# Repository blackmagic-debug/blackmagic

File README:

See https://github.com/blacksphere/blackmagic/wiki

Join the chat at https://gitter.im/blacksphere/blackmagic

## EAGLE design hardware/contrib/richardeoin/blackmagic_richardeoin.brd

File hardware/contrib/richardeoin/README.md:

This variant attempts to be as faithful to the Blackmagic mini as
possible, but also has several differences. This board has been built
and functions.

![Blackmagic richardeoin PCB](blackmagic_richardeoin_board.png
 "Blackmagic richardeoin PCB")
![Blackmagic richardeoin Assembled](blackmagic_richardeoin_assembled.JPG
 "Blackmagic richardeoin Assembled")

## Details

* The schematic and board have both been designed using Cadsoft EAGLE
  v6.4.0.

* The board size is 40mm x 16mm.

* The programming connector is an ARM 10-PIN Interface as described
  [here](http://www.keil.com/support/man/docs/ulink2/ulink2_hw_connectors.htm).

## Differences

### Uses 0603 [1608 Metric] components

The layout is intended for reflow soldering.

### Includes Level Translator

This board incorporates the same level translator used in the
full-sized Blackmagic, so it can be used to safely program 2.7V or
1.8V systems.

### USART Connector

The STM32F103's USART1 peripheral is broken out into a 0.1"
header. The hole centres are
[slightly offset to allow a press-fit](https://www.sparkfun.com/tutorials/114).

### BOOT0 Button

As well as the standard button for entering USB DFU mode, this variant
also provides a button for pulling the BOOT0 pin high to activate the
STM32 SystemMemory bootloader. Hold this button when plugging in the
module to enter then bootloader mode. Then
[scripts/bootprog.py](scripts/bootprog.py) can be used to program and
reprogram the chip over the USART1 interface.

This is useful for programming a brand new or 'bricked' blackmagic
with the DFU firmware (src/blackmagic_dfu.bin), the standard DFU mode
should be used for regular firmware updates.

## Parts and Costings

* [Parts List](Parts.md)

Parts Cost (Approximate): £14 + VAT
([uk.farnell.com](http://uk.farnell.com) August 2013)

Programming Cable: £8.49 + VAT
([uk.farnell.com](http://uk.farnell.com/samtec/ffsd-05-d-06-00-01-n/ribbon-cable-idc-152-4mm-grey-10way/dp/1667659)
August 2013)

## Assembly Photos

### Blank PCB:

### Solder Paste Stencil:

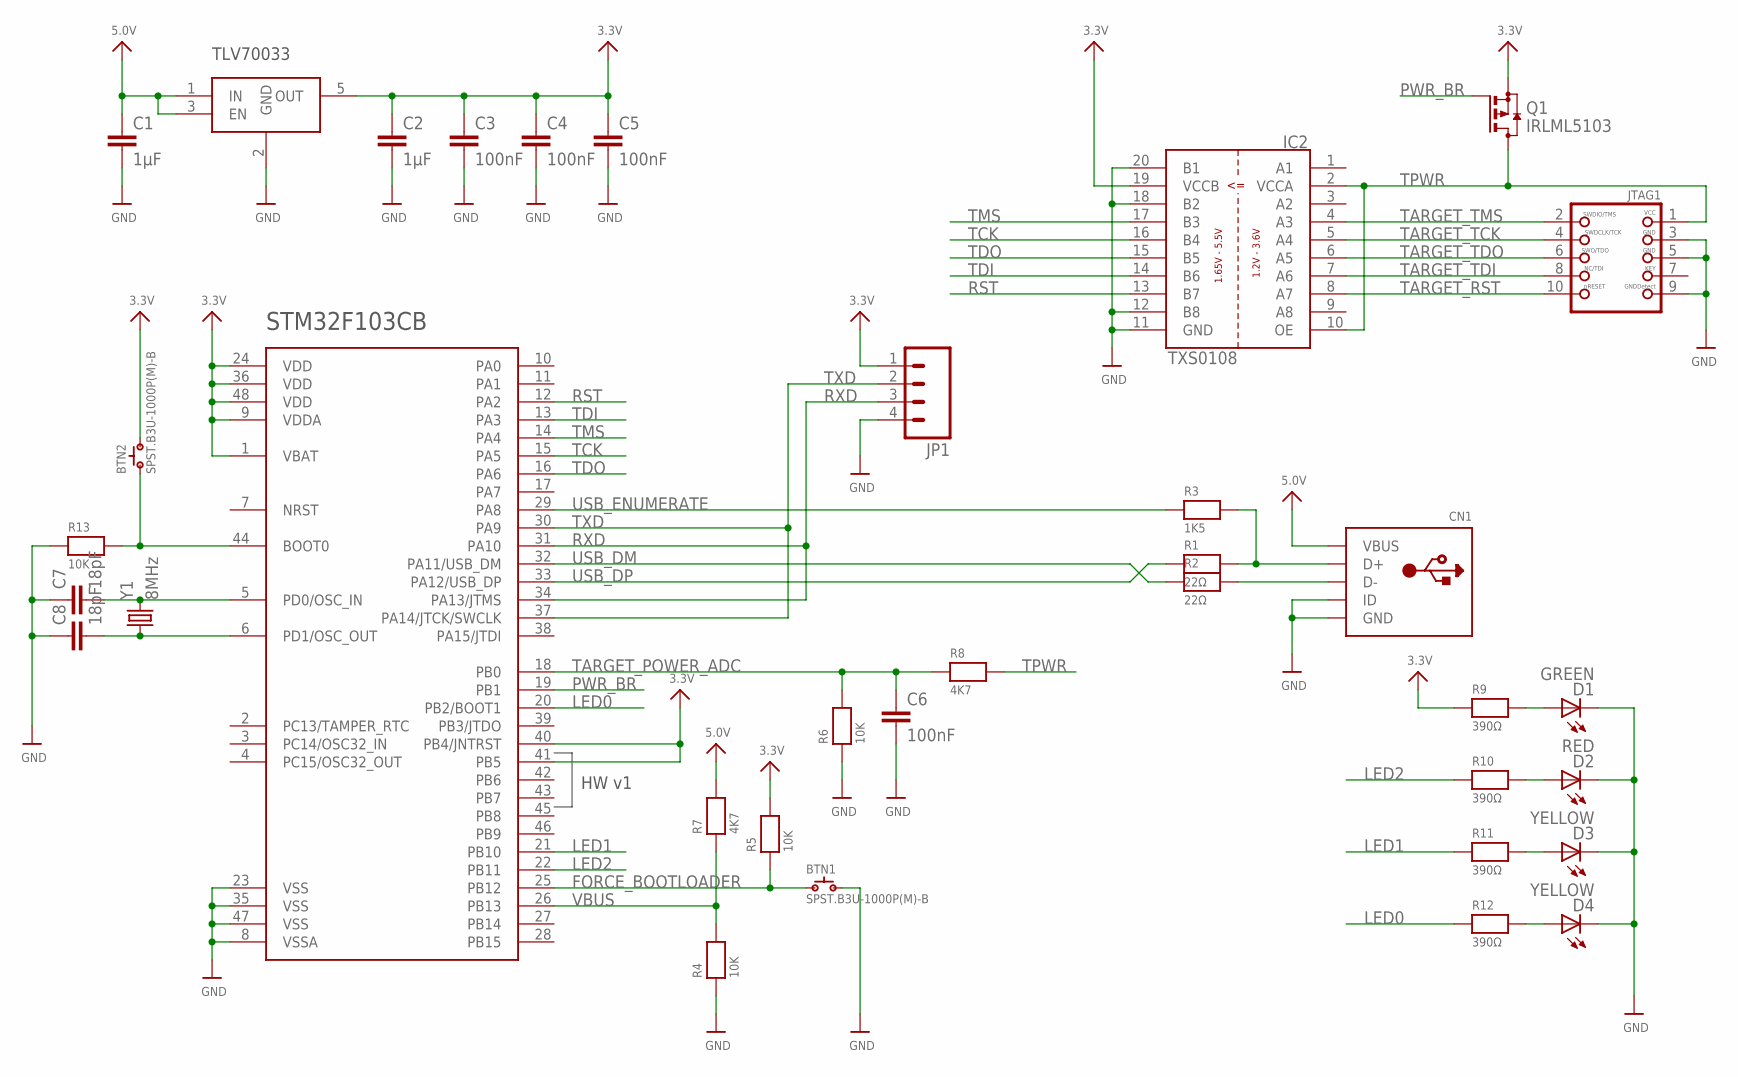
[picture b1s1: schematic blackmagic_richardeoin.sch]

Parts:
BTN1, BTN2: SPST.B3U-1000P(M)-B; B3U-1000P(M)-B
C1, C2: 1µF; C0603K
C3, C4, C5, C6: 100nF; C0603K
C7, C8: 18pF; C0603K
CN1: USBMINIB; USB-MINIB
D1: GREEN; CHIPLED_0603
D2: RED; CHIPLED_0603
D3, D4: YELLOW; CHIPLED_0603
IC1: STM32F_48PIN; TQFP48
IC2: TXS0108; TSSOP20
IC3: TLV70033DCK; SC70-5L
JP1: M04LOCK; 1X04_LOCK
JTAG1: JTAG-CORTEXM3; 2X05_1.27MM_SMT
Q1: IRLML5103; SOT23
R1, R2: 22Ω; 0603-MINI
R3: 1K5; 0603-MINI
R4, R5, R6, R13: 10K; 0603-MINI
R7, R8: 4K7; 0603-MINI
R9, R10, R11, R12: 390Ω; 0603-MINI
Y1: 8MHz; CRYSTAL-SMD-5X3

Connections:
3.3V: BTN2.2, C2.1, C3.1, C4.1, C5.1, IC1.1 (VBAT), IC1.9 (VDDA), IC1.24 (VDD), IC1.36 (VDD), IC1.40 (PB4/JNTRST), IC1.41 (PB5), IC1.48 (VDD), IC2.19 (VCCB), IC3.5 (OUT), JP1.1, Q1.2 (S), R5.2, R9.1
5.0V: C1.1, CN1.VBUS, IC3.1 (IN), IC3.3 (EN), R7.2
BOOT0: BTN2.1, IC1.44 (BOOT0), R13.2
D+: CN1.D+, R1.2, R3.2
D-: CN1.D-, R2.2
FORCE_BOOTLOADER: BTN1.1, IC1.25 (PB12), R5.1
GND: BTN1.2, C1.2, C2.2, C3.2, C4.2, C5.2, C6.2, C7.1, C8.1, CN1.GND, CN1.ID, D1.C, D2.C, D3.C, D4.C, IC1.8 (VSSA), IC1.23 (VSS), IC1.35 (VSS), IC1.47 (VSS), IC2.11 (GND), IC2.12 (B8), IC2.18 (B2), IC2.20 (B1), IC3.2 (GND), JP1.4, JTAG1.3, JTAG1.5, JTAG1.9, R4.1, R6.1, R13.1
LED0: IC1.20 (PB2/BOOT1), R12.1
LED1: IC1.21 (PB10), R11.1
LED2: IC1.22 (PB11), R10.1
LPC_XTAL2: C8.2, IC1.6 (PD1/OSC_OUT), Y1.1
unnamed: D2.A, R10.2
unnamed: D1.A, R9.2
unnamed: D3.A, R11.2
unnamed: D4.A, R12.2
OSC_IN: C7.2, IC1.5 (PD0/OSC_IN), Y1.3 (2)
PWR_BR: IC1.19 (PB1), Q1.1 (G)
RST: IC1.12 (PA2), IC2.13 (B7)
RXD: IC1.31 (PA10), IC1.34 (PA13/JTMS), JP1.3
TARGET_POWER_ADC: C6.1, IC1.18 (PB0), R6.2, R8.1
TARGET_RST: IC2.8 (A7), JTAG1.10
TARGET_TCK: IC2.5 (A4), JTAG1.4
TARGET_TDI: IC2.7 (A6), JTAG1.8
TARGET_TDO: IC2.6 (A5), JTAG1.6
TARGET_TMS: IC2.4 (A3), JTAG1.2
TCK: IC1.15 (PA5), IC2.16 (B4)
TDI: IC1.13 (PA3), IC2.14 (B6)
TDO: IC1.16 (PA6), IC2.15 (B5)
TMS: IC1.14 (PA4), IC2.17 (B3)
TPWR: IC2.2 (VCCA), IC2.10 (OE), JTAG1.1, Q1.3 (D), R8.2
TXD: IC1.30 (PA9), IC1.37 (PA14/JTCK/SWCLK), JP1.2
USB_DM: IC1.32 (PA11/USB_DM), R2.1
USB_DP: IC1.33 (PA12/USB_DP), R1.1
USB_ENUMERATE: IC1.29 (PA8), R3.1
VBUS: IC1.26 (PB13), R4.2, R7.1

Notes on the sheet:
STM32F103CB
HW v1
TLV70033

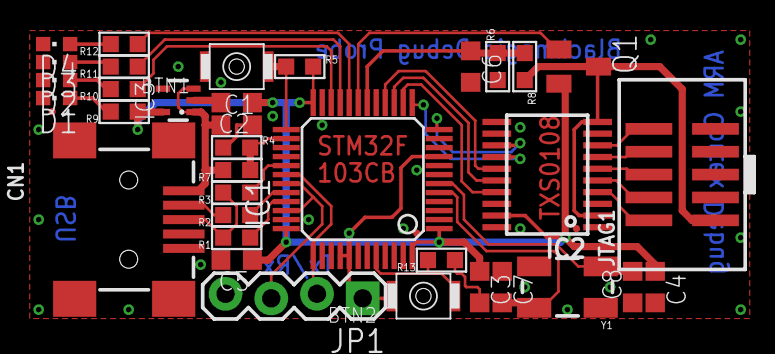
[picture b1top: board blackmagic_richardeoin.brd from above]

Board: 2 copper layers, 35 parts (0 on the bottom side), 35 nets.

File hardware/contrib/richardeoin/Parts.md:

## Parts List

| ID | Part Number | Description | Supplier | Order Code | Quantity
| --- | --- | --- | --- | --- | ---
| IC1 | STM32F103CBT6 | Microcontroller, 128Kb Flash, 20Kb SRAM, -40 to 85°C | Farnell | [1606327](http://uk.farnell.com/jsp/search/browse.jsp;jsessionid=0?N=0&Ntk=partnumbers&Ntt=*1606327*) | 1
| JTAG1 | 20021121-00010C4LF | 2x5 Pin Header, SMT, 1.27mm Pitch, Gold Plate | Farnell | [1865279](http://uk.farnell.com/jsp/search/browse.jsp;jsessionid=0?N=0&Ntk=partnumbers&Ntt=*1865279*) | 1
| N/A | FFSD-05-D-06.00-01-N | Ribbon Cable 6", Grey, 10 way, 1.27mm Pitch | Farnell | [1667659](http://uk.farnell.com/jsp/search/browse.jsp;jsessionid=0?N=0&Ntk=partnumbers&Ntt=*1667659*) | 1
| CN1 | 67503-1230 | USB Mini B Receptacle, SMT | Farnell | [2313554](http://uk.farnell.com/jsp/search/browse.jsp;jsessionid=0?N=0&Ntk=partnumbers&Ntt=*2313554*) | 1
| BTN1 | B3U-1000P-B | SPST-NO Switch, SMD | Farnell | [1333654](http://uk.farnell.com/jsp/search/browse.jsp;jsessionid=0?N=0&Ntk=partnumbers&Ntt=*1333654*) | 1
| Q1 | IRLML5103PBF | MOSFET, P, -30V, -0.61A, SOT-23 | Farnell | [8660085](http://uk.farnell.com/jsp/search/browse.jsp;jsessionid=0?N=0&Ntk=partnumbers&Ntt=*8660085*) | 1
| IC2 | TXS0108EPWR | Bidirectional Voltage Translator, 8-bit, 20TSSOP | Farnell | [1702548](http://uk.farnell.com/jsp/search/browse.jsp;jsessionid=0?N=0&Ntk=partnumbers&Ntt=*1702548*) | 1
| IC3 | TLV70033DCKT | LDO Regulator, 3.3V 200mA, 5SC70 | Farnell | [1815750](http://uk.farnell.com/jsp/search/browse.jsp;jsessionid=0?N=0&Ntk=partnumbers&Ntt=*1815750*) | 1
| Y1 | ABMM2-8.000MHZ-E2-T | Crystal, 8MHz, 18pF, 6x3.6mm | Farnell | [1611803](http://uk.farnell.com/jsp/search/browse.jsp;jsessionid=0?N=0&Ntk=partnumbers&Ntt=*1611803*) | 1
| R1, R2 | MC0063W0603122R | Resistor 22Ω, 0.063W, 1%, 0603 [1608 Metric] | Farnell | [9330844](http://uk.farnell.com/jsp/search/browse.jsp;jsessionid=0?N=0&Ntk=partnumbers&Ntt=*9330844*) | 2
| R3 | MC0063W060311K5 | Resistor 1.5KΩ, 0.063W, 1%, 0603 [1608 Metric] | Farnell | [9330607](http://uk.farnell.com/jsp/search/browse.jsp;jsessionid=0?N=0&Ntk=partnumbers&Ntt=*9330607*) | 1
| R4, R5, R6 | MC0063W0603110K | Resistor 10KΩ, 0.063W, 1%, 0603 [1608 Metric] | Farnell | [9330399](http://uk.farnell.com/jsp/search/browse.jsp;jsessionid=0?N=0&Ntk=partnumbers&Ntt=*9330399*) | 3
| R7, R8 | MC0063W060314K7 | Resistor 4.7KΩ, 0.063W, 1%, 0603 [1608 Metric] | Farnell | [9331247](http://uk.farnell.com/jsp/search/browse.jsp;jsessionid=0?N=0&Ntk=partnumbers&Ntt=*9331247*) | 2
| R9, R10, R11, R12 | MC0063W06031390R | Resistor 390Ω, 0.063W, 1%, 0603 [1608 Metric] | Farnell | [9331131](http://uk.farnell.com/jsp/search/browse.jsp;jsessionid=0?N=0&Ntk=partnumbers&Ntt=*9331131*) | 4
| D1 | KPT-1608SGC | LED, Green 568nm, 0603 [1608 Metric] | Farnell | [2099223](http://uk.farnell.com/jsp/search/browse.jsp;jsessionid=0?N=0&Ntk=partnumbers&Ntt=*2099223*) | 1
| D2 | KPT-1608EC | LED, Red 625nm, 0603 [1608 Metric] | Farnell | [2099221](http://uk.farnell.com/jsp/search/browse.jsp;jsessionid=0?N=0&Ntk=partnumbers&Ntt=*2099221*) | 1
| D3, D4 | KPT-1608YC | LED, Yellow 588nm, 0603 [1608 Metric] | Farnell | [2099227](http://uk.farnell.com/jsp/search/browse.jsp;jsessionid=0?N=0&Ntk=partnumbers&Ntt=*2099227*) | 2
| C1, C2 | MC0603X105K100CT | Capacitor 1µF, X5R, 10V, 0603 [1608 Metric] | Farnell | [1759399](http://uk.farnell.com/jsp/search/browse.jsp;jsessionid=0?N=0&Ntk=partnumbers&Ntt=*1759399*) | 2
| C3, C4, C5, C6 | MC0603B104K500CT | Capacitor 100nF, X7R, 50V, 0603 [1608 Metric] | Farnell | [1759122](http://uk.farnell.com/jsp/search/browse.jsp;jsessionid=0?N=0&Ntk=partnumbers&Ntt=*1759122*) | 4
| C7, C8 | MC0603N180J500CT | Capacitor 18pF, C0G / NP0, 50V, 0603 [1608 Metric] | Farnell | [1759056](http://uk.farnell.com/jsp/search/browse.jsp;jsessionid=0?N=0&Ntk=partnumbers&Ntt=*1759056*) | 2

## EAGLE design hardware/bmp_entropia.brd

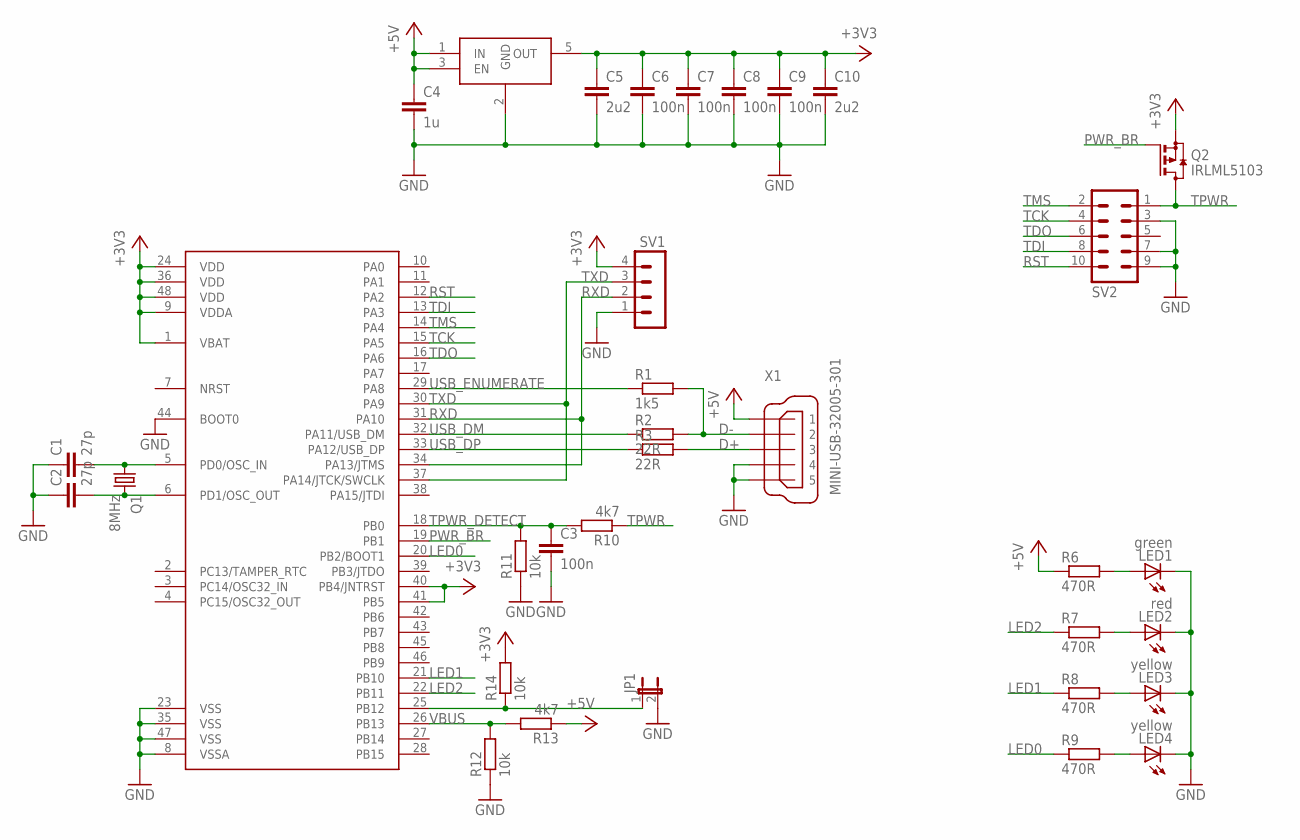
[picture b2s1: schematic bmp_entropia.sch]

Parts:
C1, C2: 27p; C0603
C3, C6, C7, C8, C9: 100n; C0603
C4: 1u; C0603
C5, C10: 2u2; C0603
JP1: JP1E; JP1
LED1: green; CHIPLED_0603
LED2: red; CHIPLED_0603
LED3, LED4: yellow; CHIPLED_0603
Q1: 8MHz; HC49/S
Q2: IRLML5103; SOT23
R1: 1k5; R0603
R2, R3: 22R; R0603
R6, R7, R8, R9: 470R; R0603
R10, R13: 4k7; R0603
R11, R12, R14: 10k; R0603
SV1: MA04-1
SV2: MA05-2
U$1: STM32F_48PIN; TQFP48
U$2: TLV70033DCK; SC70-5L
X1: MINI-USB-32005-301; 32005-301

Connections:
+3V3: C5.1, C6.1, C7.1, C8.1, C9.1, C10.1, Q2.2 (S), R14.2, SV1.4, U$1.1 (VBAT), U$1.9 (VDDA), U$1.24 (VDD), U$1.36 (VDD), U$1.40 (PB4/JNTRST), U$1.41 (PB5), U$1.48 (VDD), U$2.5 (OUT)
+5V: C4.1, R6.1, R13.1, U$2.1 (IN), U$2.3 (EN), X1.1
D+: R3.2, X1.3
D-: R1.2, R2.2, X1.2
GND: C1.1, C2.1, C3.2, C4.2, C5.2, C6.2, C7.2, C8.2, C9.2, C10.2, JP1.2, LED1.C, LED2.C, LED3.C, LED4.C, R11.1, R12.1, SV1.1, SV2.3, SV2.7, SV2.9, U$1.8 (VSSA), U$1.23 (VSS), U$1.35 (VSS), U$1.44 (BOOT0), U$1.47 (VSS), U$2.2 (GND), X1.4, X1.5
LED0: R9.1, U$1.20 (PB2/BOOT1)
LED1: R8.1, U$1.21 (PB10)
LED2: R7.1, U$1.22 (PB11)
LED_G: LED1.A, R6.2
LED_R: LED2.A, R7.2
LED_Y0: LED4.A, R9.2
LED_Y1: LED3.A, R8.2
OSC_IN: C1.2, Q1.1, U$1.5 (PD0/OSC_IN)
OSC_OUT: C2.2, Q1.2, U$1.6 (PD1/OSC_OUT)
PWR_BR: Q2.1 (G), U$1.19 (PB1)
RST: SV2.10, U$1.12 (PA2)
RXD: SV1.2, U$1.31 (PA10), U$1.34 (PA13/JTMS)
TASTER: JP1.1, R14.1, U$1.25 (PB12)
TCK: SV2.4, U$1.15 (PA5)
TDI: SV2.8, U$1.13 (PA3)
TDO: SV2.6, U$1.16 (PA6)
TMS: SV2.2, U$1.14 (PA4)
TPWR: Q2.3 (D), R10.1, SV2.1
TPWR_DETECT: C3.1, R10.2, R11.2, U$1.18 (PB0)
TXD: SV1.3, U$1.30 (PA9), U$1.37 (PA14/JTCK/SWCLK)
USB_DM: R2.1, U$1.32 (PA11/USB_DM)
USB_DP: R3.1, U$1.33 (PA12/USB_DP)
USB_ENUMERATE: R1.1, U$1.29 (PA8)
VBUS: R12.2, R13.2, U$1.26 (PB13)

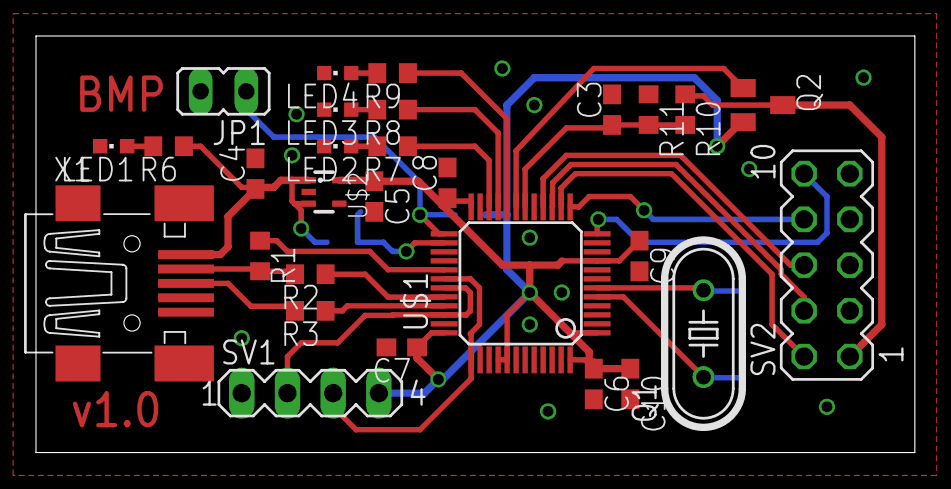
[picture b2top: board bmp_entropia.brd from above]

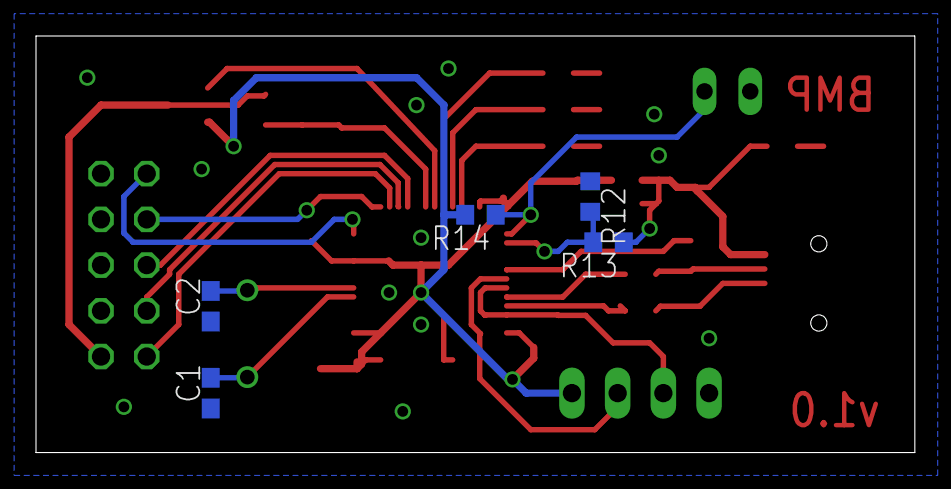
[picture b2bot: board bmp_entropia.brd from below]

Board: 2 copper layers, 48.8 x 23.1 mm, 34 parts (5 on the bottom side), 29 nets.

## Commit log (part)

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2026-02-11 common/aux_serial: Implemented more of the multi-UART logic for hooking the dual target serial interfaces up to the second host serial interface
2026-02-11 bmp-v3: Handle proper initialisation of the bus direction pins
2026-02-11 common/swdptap: Small tweak to where the read happens in the I/O cycle for SWD in
2026-02-11 common/aux_serial: Impelemented the UART1 half of the switchable UART mechanism using the EXTI
2026-02-11 common/aux_serial: Fixed an order of includes error that meant certain steering macros weren't available when they should be
2026-02-12 riscv_debug: Log tdata2 from discovered triggers during probe (to detect if any were in use)
2026-02-12 riscv_debug: Unconditionally disable triggers during detach
2026-02-18 hosted/ftdi: Add Description string of "arm-usb-ocd-h", expand comments.
2026-02-18 hosted/ftdi: Block-move "arm-usb-ocd" below "arm-usb-ocd-h", add FS "arm-usb-tiny"
    * 15b1:0003 "olimex" is the original "Olimex OpenOCD JTAG" aka ARM-USB-OCD,
    so give it a specific name and reference its usermanual by hyperlinks.
    Add description string. This seems to be a full prefix of 3 others, so make it the last entry.
    * 15b1:0004 also exists, it's Olimex OpenOCD JTAG TINY" aka ARM-USB-TINY,
    the unbuffered version. No reason to omit support for it.
2026-02-19 bmp-v3: Begun fleshing out the platform definitions for the pinout
2026-02-19 adiv5_swd: Fixed some issues in the copyright header
2026-02-19 bmp-v3: Started filling in interrupt setup and control macros
2026-02-22 bmp-v3: Defined the DMA setup for the SWO and AUX UART subsystems
2026-02-22 common/aux_serial: Implemented support for sourcing data from two UARTs and switching between them automatically
2026-02-22 common/swo_manchester: Handle the STM32U5 timer input multiplexing properly
2026-02-22 bmp-v3: Added a linker script for the platform
2026-02-22 bmp-v3: Begun implementing the platform-specific functions
2026-02-22 bmp-v3: Implemented the boot request logic
2026-02-22 bmp-v3: Defined the first part of platform initialisation, bringing up USB, timing, and setting up the correct vector table address
2026-02-22 stlinkv3: Removed a duplicated include line
2026-02-22 common: Cleaned up the core DFU bootloader using the buffer_utils header
2026-02-22 bmp-v3: Built out the bootloader for the platform
2026-02-22 common: Enabled the STM32U5 in the core DFU bootloader
2026-02-22 common: Enable the USB DFU stub to properly reboot cores that are ARMv8-M main profile
2026-02-22 bmp-v3: Initialise the LED pins so we can see the GDB machinary state
2026-02-22 misc: Turn off a clang-analyzer-core lint that we cannot avoid due to writing firmware
2026-02-22 bmp-v3: Implemented target power support
2026-02-22 bmp-v3: More GPIO initialisation work, making sure nRST is bought up correctly and the pins are driven suitably hard
2026-02-22 bmp-v3: Implemented logic for enabling and disabling the secondary UART appropriately based on state changes
2026-02-23 f072/atomic: Implemented compare-exchange and fetch-add for 32-bit unsigned values
2026-02-23 stm32l4: Enable non-halting I/O for the STM32U5 parts as there are no noticable ill effects
    This needs properly documenting and that documentation must be written before this is PR'd. The flag does not cause data corruption and appears to work the correct way, however it's unknown if it's a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
2026-02-23 gdb_main: Fix a comment style issue in exec_q_memory_map()
2026-02-24 github: Switched size-diff over to BMPv3 in the PR workflow
2026-02-24 github: Updated the version of the ARM toolchain we CI with (14.3 -> 15.2)
2026-02-24 github: Updated the actions version pinnings in the build-and-upload flow
2026-02-25 target: Built out a function for building the target memory map in chunks
2026-03-05 stm32f1: Hardcode GD32VW553 memory map
2026-03-08 misc: update links github to codeberg
2026-03-09 hosted/bmp_serial: Prevent the RegGetValue() call that fills the output string with its value from getting compiled out when assertions are off
2026-03-09 mspm0: Compress the FACTORY/BCR register description table
2026-03-09 mspm0: Expand the id list of supported mspm0 targets
2026-03-14 target: Simplified the Flash memory entry formatter, shaving some size off the binary and fixing it being grumpy if the length parameter was 0
2026-03-14 riscv_debug: Fixed some type conversions lints in the target description builder function
2026-03-16 remote: Fix a comment carrying the incorrect command characters for a command (JTAG run cycles command)
2026-03-16 common/jtagtap: Avoid running any cycles if we're asked to do nothing with `jtagtap_cycle()`
2026-03-17 codeberg: Implemented steps for building BMDA on Linux with both Clang and GCC
2026-03-18 codeberg: Enabled LTO for the Linux BMDA builds
2026-03-18 codeberg: Implemented steps for building BMDA for Windows from Linux
2026-03-22 remote: Begun to switch the remote protocol to be expressed in terms of the GDB packet structure
2026-03-22 remote: Converted the general packet handler to be expressed in terms of the GDB packet structure
2026-03-22 gdb_packet: Converted consume_remote_packet() to using the new GDB packet structure
2026-03-22 remote: Converted the RISC-V packet handler to be expressed in terms of the GDB packet structure
2026-03-22 gdb_packet: Fixed a clang-tidy warning about type conversions in the GDB escape char handling
2026-03-23 cortexm: wait for halt
    fixes #2155
2026-03-25 riscv_debug: Reorder editing triggers *after* the halting
    * Any CSR access is only possible on a halted hard
    * Violating the order results in 4 (wrong state)
2026-03-27 nrf54l: Enable non-halting SRAM access for RTT on nRF54L series
2026-03-27 stm32f1: Enable non-halting SRAM access for RTT on AT32F403A/F407
2026-03-27 stm32f1: Enable non-halting SRAM access for RTT on AT32F425
2026-03-27 stm32g0: Enable non-halting SRAM access for RTT on G0/C0 series
    * Tested on STM32G071RB
2026-03-29 README: Update the CI badge to use the codeberg CI instead of GH.
2026-03-29 riscv_debug: Step over ebreak instructions
2026-03-29 riscv_debug: Give names to semihosting NOPs and GPR A1
    * Use small regno in riscv_hostio_request
2026-03-29 cortexar: Make attach/detach visible in headers
2026-03-30 stm32mp15: Add a command to configure SWO parameters over AP1
2026-03-30 common/swdptap: Ensure TDI is driven high, as spec allows it (as-if undriven)
2026-04-05 stm32mp15: Postpone allocating AXI-AP to ca7_attach()
2026-04-05 stm32mp15: Restore CA7 memory access methods on detach
2026-04-05 stm32mp15: Always use AP1 for conf_swo
2026-04-05 at32f43x: Implement read unprotect over SWD transport
2026-04-05 adi, cortex: Add Cortex-A55 identifiers
2026-04-05 swlink: Implement SWCLK self-measurement as a platform command
2026-04-05 swlink: timing: Update routines for stm32f103 flash
2026-04-05 native: Implement spi_xfer_block for faster reads
2026-04-05 stlink, swlink: Add no-op stubs for spi_xfer_block
2026-04-05 cortexm, cortexar: Report malloc failures in target_description
2026-04-05 blackpill-f4: Extract macros for VTRef pin and channel
2026-04-05 blackpill-f4: split adc conversions
    * Power-off ADC after use (only used upon target scan)
    * Prescale ADC1 clock (APB2) by 4
    * Refactor regular sequence of 2 channels into two launches
2026-04-06 stlink: document stlink v2-1 bootloader behavior
2026-04-09 hosted/remote/protocol_v4: Add JTAG ensure idle command (!JI#)
2026-04-09 stm32mp15: Read DBGMCU for CA7 via AP1
2026-04-12 riscv32: Prepare memory access via progbuf
2026-04-13 riscv32: Delegate to riscv_csr_read/write in riscv32_progbuf_mem_read/write for AAR
2026-04-13 riscv32: Use newly added RV_GPR_A1
2026-04-13 riscv32: Update riscv32_progbuf_mem_read to use both x10 & x11
2026-04-13 riscv32: Restore saved GPR A0,A1 on progbuf_mem errors in the loop
2026-04-14 jtag_devs: Register Hazard3/ice40 TAP as a RISC-V DTM
2026-04-16 riscv_debug: Preserve already set hart flags when enabling SysBus
2026-04-20 misc: Support for STM32401CD Blackpill as debug probe
2026-04-20 bmp-v3: Properly handle disabling either UART with the platform function for disabling them
2026-04-20 bmp-v3: Pruned the now unused functions for UART control and cleaned up in the initialisation logic
2026-04-20 bmp-v3: Implemented a command for setting the BMDU connector's UART pin swapping state
2026-04-20 common/aux_serial: Moved the UART state tracking into the main UART implementation where it belongs, simplifying and finishing correcting the UART handling for BMPv3
2026-04-20 common/usb_serial: Documentation for parts of how the debug and aux serial transmit components work
2026-04-20 common/usb_serial: Fix the debug serial logic doing a bad by turning USB interrupts off while trying to send data (this breaks DWC2 packet queueing)
2026-04-20 bluepillplus: Add chip detection and faster PLL configs
    * Rely on DBGMCU_IDCODE and SCB_CPUID
2026-04-20 bluepillplus: Add chip detection via CoreSight ROM tables
2026-04-23 buffer-utils: Added `read_le8`
2026-04-25 general: Added `__has_builtin` check for `__builtin_constant_p`
2026-04-25 buffer: Added `reverse_bits` helpers for `8`/`16`/`24`/`32` bit widths
    There is currently only a single optimized path for arm using `rbit` but others for other platforms should be added as these are kinda expensive instruction wise,
    Not a huge deal on BMDA, but any other probe that is not an Arm with `rbit` is going to be in for some real pain
2026-04-25 lattice_ecp5: Mark things that were supposed to be static actually static
2026-04-26 lattice_ecp5: Fixed up the order of flash operations to ensure SRAM programming succeeds
2026-04-26 lattice_ecp5: Fix identification of attached SPI flash
2026-04-26 lattice_ecp5: Prevent the ECP5 from becoming a zombie
2026-04-26 stm32h7rs: DBGMCU stuff in attach/detach was causing problems. Disabled.
2026-04-26 stm32h7rs: align w/ latest H7 driver, clean out unused stuff.
2026-04-26 Added copyright and psize changes requested.
2026-04-26 stm32h7rs: fix formatting issues found by CI
2026-04-28 stm32c5: Fix bug in C5 revision reporting.
2026-05-01 codeberg: Created a new CI flow for the `lint` step we did on GHA, allowing pre-commit to run again
2026-05-01 lattice_ecp5: Fixed the formatting lints from `pre-commit`
2026-05-02 lattice_ecp5: Fixed hex literal case lints from `pre-commit`
2026-05-02 adiv5: Fixed the formatting lint from `pre-commit`
2026-05-05 stm32u3: fix sram2 region logic per ALTracer
2026-05-05 stm32u3: initial checkin of stm32u3 support - probes, attaches, debugs, reads but erase, write fail
2026-05-05 riscv_debug: Fix stack buffer overflow in 128-bit CSR access
2026-05-07 bmp-v1: add `bmp-v1` cross-files files referencing `bmp-v2` to make backwards compatibility less ambiguous
2026-05-12 swlink: Do not wait for RST pin level to change in nrst_set_val()
2026-05-13 ftdi: Fixed a bug in the `ftdi_jtag_tdi_tdo_seq` that wasn't taking the `final_tms` adjustment for `bits` into account

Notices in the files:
parts and their libraries:
microbuilder_v3: This work is placed in the public domain, and may be freely used for commercial and non-commercial work with the following conditions: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
SparkFun: Licensing: CC v3.0 Share-Alike You are welcome to use this library for commercial purposes.
